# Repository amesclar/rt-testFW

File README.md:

# Sailing Regatta Timer - Automated Test Framework

- [Sailing Regatta Timer - Automated Test Framework](#sailing-regatta-timer---automated-test-framework)
  - [Key Features](#key-features)
  - [Measuring 12v](#measuring-12v)
  - [Flow Diagram](#flow-diagram)
  - [Board and Wiring](#board-and-wiring)
    - [Schematic](#schematic)
    - [PCB](#pcb)

## Key Features

- automated routine that exercises sailing regatta timer while monitoring buzzer activation (horn voltage)
- test board connected to computer that monitors serial port
- measures and logs horn voltage

## Measuring 12v

```text
V_out = V_in × (R2 / (R1 + R2))

R1 = 10kΩ
R2 = 5k1
```

Ratio: 2:1 (divides voltage by 3)
Output at 12V input: 4V

## Flow Diagram

## Board and Wiring

### Schematic

### PCB

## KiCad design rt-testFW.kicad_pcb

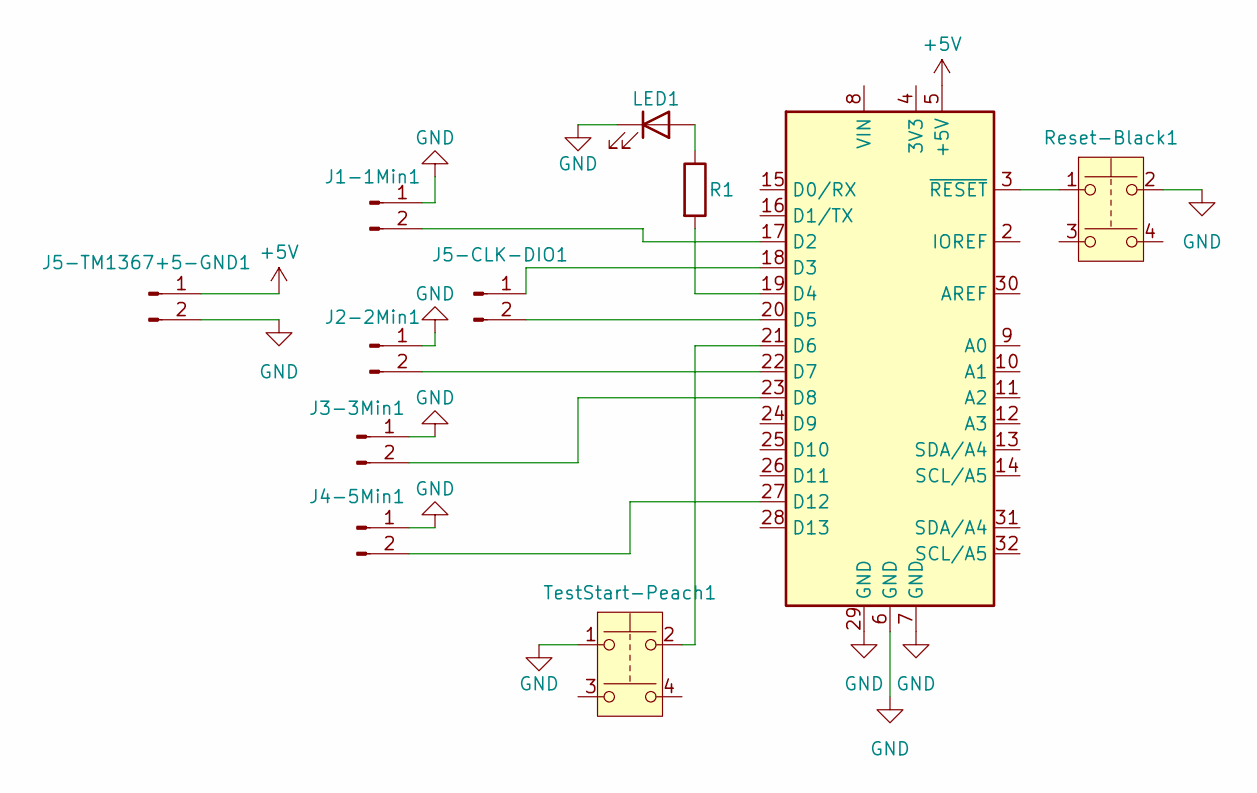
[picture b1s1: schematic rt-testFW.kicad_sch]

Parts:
A1: Arduino_UNO_R3
J1-1Min1, J2-2Min1, J3-3Min1, J4-5Min1, J5-CLK-DIO1, J5-TM1367+5-GND1: Conn_01x02_Male; PinSocket_1x02_P2.54mm_Vertical
LED1: LED; PinHeader_1x02_P2.00mm_Vertical
R1: R; PinHeader_1x02_P2.00mm_Vertical
Reset-Black1: SW_Push_Dual; SW_PUSH_6mm
TestStart-Peach1: SW_Push_Dual; SW_PUSH_6mm

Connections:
+5V: A1.5 (+5V), J5-TM1367+5-GND1.1
GND: A1.6 (GND), A1.7 (GND), A1.29 (GND), J1-1Min1.1, J2-2Min1.1, J3-3Min1.1, J4-5Min1.1, J5-TM1367+5-GND1.2, LED1.1 (K), Reset-Black1.2, TestStart-Peach1.1
unnamed: A1.17 (D2), J1-1Min1.2
unnamed: A1.18 (D3), J5-CLK-DIO1.1
unnamed: A1.19 (D4), R1.2
unnamed: A1.20 (D5), J5-CLK-DIO1.2
unnamed: A1.21 (D6), TestStart-Peach1.2
unnamed: A1.22 (D7), J2-2Min1.2
unnamed: A1.23 (D8), J3-3Min1.2
unnamed: A1.27 (D12), J4-5Min1.2
unnamed: A1.3 (~RESET), Reset-Black1.1
unnamed: LED1.2 (A), R1.1

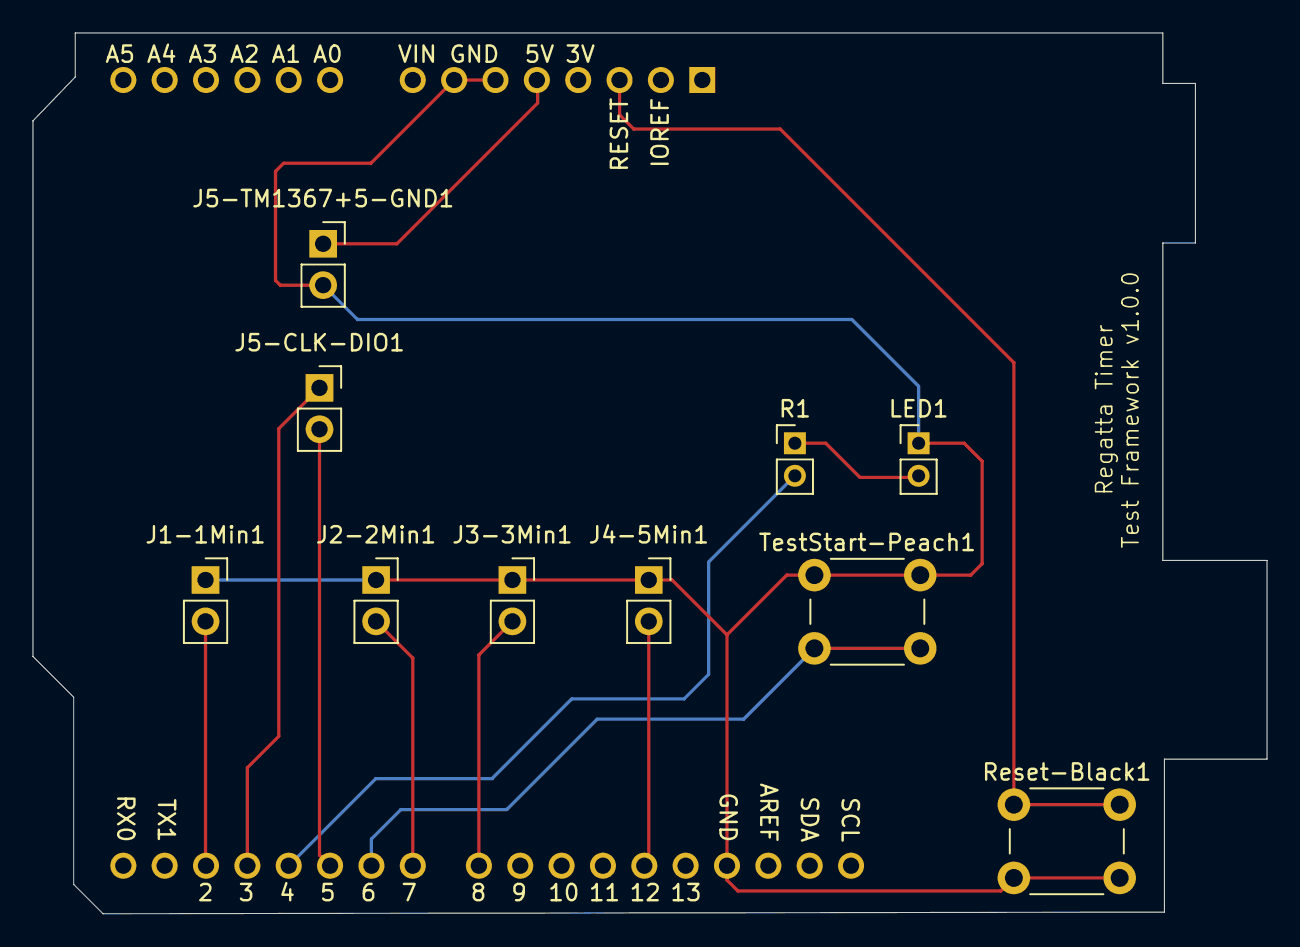
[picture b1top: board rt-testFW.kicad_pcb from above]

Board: 2 copper layers, 75.8 x 54.1 mm, 11 parts (0 on the bottom side), 12 nets.

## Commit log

2025-08-18 initial
2025-08-18 update dependencies to address security issues
2025-08-19 Bump requests from 2.32.4 to 2.32.5 in the pip group across 1 directory
    Bumps the pip group with 1 update in the / directory: [requests](https://github.com/psf/requests).
    Updates `requests` from 2.32.4 to 2.32.5
    - [Release notes](https://github.com/psf/requests/releases)
    - [Changelog](https://github.com/psf/requests/blob/main/HISTORY.md)
    - [Commits](https://github.com/psf/requests/compare/v2.32.4...v2.32.5)
    ---
2025-08-22 initial iteration complete
2025-09-09 add missed gitignore file
2025-11-20 completed run wrapper and test count validation
2025-11-23 ai generated data validation script feature complete
2025-11-24 aligned spec and code and updated both to include junit output
2025-11-30 initial claude generated code and spec
2025-12-03 feature complete - buzzer voltage measurement
2025-12-03 removed validation related files
2025-12-12 final update to support tm1637 digital output
2025-12-12 2nd commit to catch earlier missed files
2025-12-13 added label with version to pcb
2025-12-15 fixed issue - immediate 1m test start
2025-12-24 change iteration count
2026-01-05 pcb-flip complete, add custom uno library
2026-01-14 pcb relayout complete
2026-03-24 partial commit to save work in progress
2026-03-25 partial commit to save work
2026-03-25 addressed 5min duration failure
2026-03-26 incremental save
2026-03-30 voltage measurement debug complete
